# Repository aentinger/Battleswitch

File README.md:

💾 Battleswitch
===============

# 📸 Image

# 📂 Description

A battleswitch is an electronic module which is responsible for the activation/deactivation of weapon systems in combat robots. More generally spoken, a battleswitch is a module which enables the switching of loads using an ordinary remote control.

The LXRobotics Battleswitch enables the control of up to 2 actuators over a single RC remote control channel. The battleswitch is connected to and powered by the RC receiver over a 3-pin connection like a servo and tolerates a wide input voltage range from 2 to 8 V DC with a maximum current consumption of 75 mA. The internal software state of the battleswitch is visualized via LEDs, which greatly simplifies operation and integration of the battleswitch. The assignment which remote control input signal leads to which actuator output, is performed via firmware versions which are generated by LXRobotics upon request.

**Features**

* 1 Remote control channel switches 2 actuators
* Switching capacity per channel: max. 40 V / 5 A @ 100 °C
* Supply of the battleswitch electronics by the RC receiver - no additional power supply terminal necessary
* Wide input voltage range for electronic supply: 2 - 8 V DC
* Status-LEDs signal the internal software state and the current switching status
* POWER-LED lights up when there the battleswitch is supplied with power
* Failsafe - switching off the actuators in the absence of a valid remote control signal
* Freewheeling diodes available - switching of inductive loads possible
* 3 x M3 holes for stable mounting of the Battleswitch
* Small size: 50 x 50 mm (L x W)

# 🎥 [Video](images/battleswitch_demo.mp4)

# 💻 Build
```bash
sudo apt-get install cmake avr-libc binutils-avr gcc-avr avrdude
git clone https://github.com/aentinger/Battleswitch && cd Battleswitch/software
mkdir build && cd build
cmake ..
make
```

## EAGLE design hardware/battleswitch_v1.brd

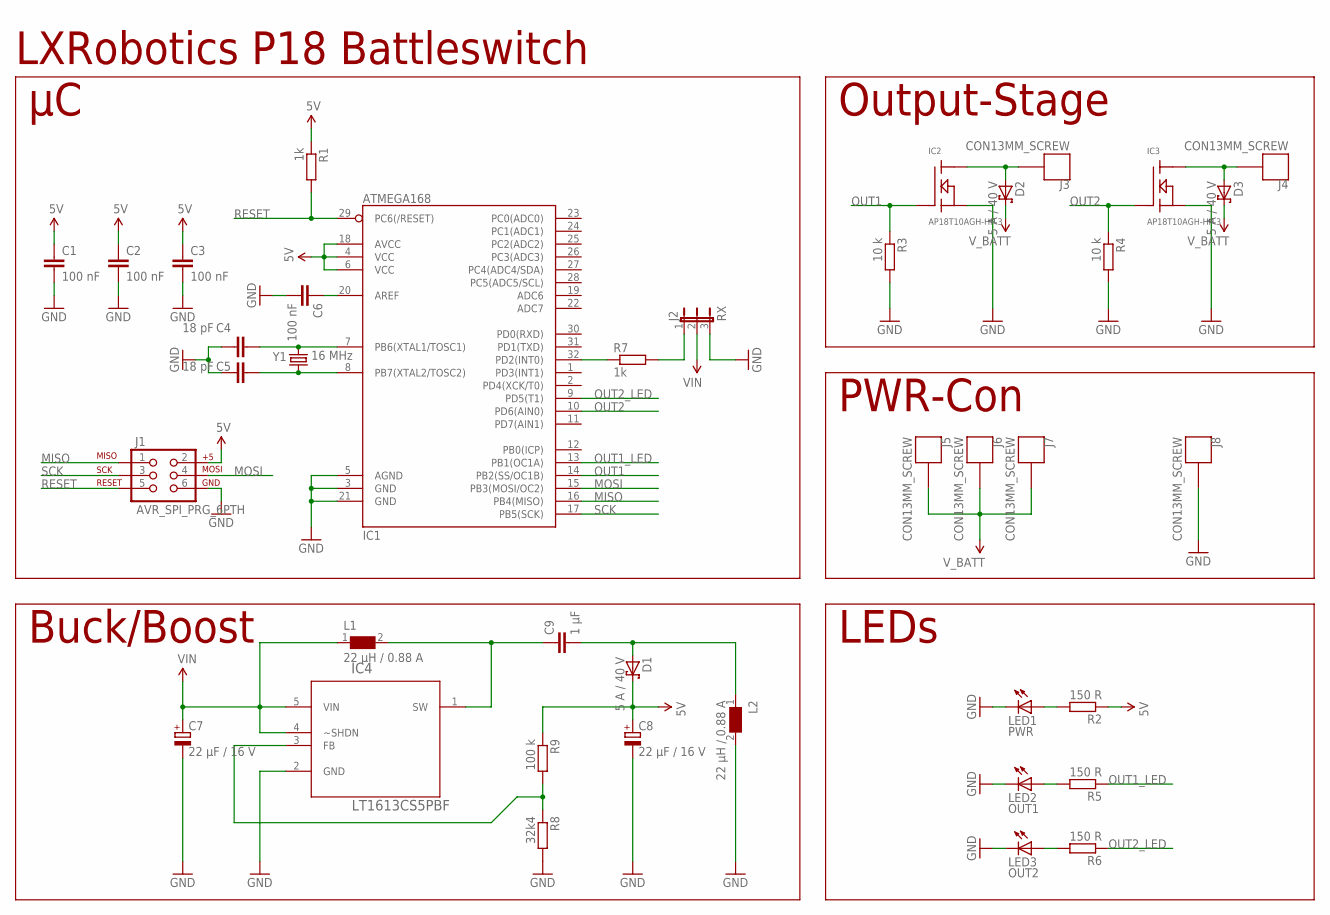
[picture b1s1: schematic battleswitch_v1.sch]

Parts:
C1, C2, C3, C6: 100 nF; C0805
C4, C5: 18 pF; C0805
C7, C8: 22 µF / 16 V; PANASONIC_C
C9: 1 µF; C0805
D1, D2, D3: 5 A / 40 V; SMC
IC1: ATMEGA168; TQFP32-08
IC2, IC3: AP18T10AGH-HF-3; TO252
IC4: LT1613CS5PBF; SOT95P280X145-5N
J1: AVR_SPI_PRG_6PTH; 2X3
J2: RX; JP2
J3, J4, J5, J6, J7, J8: CON13MM_SCREW; CON1_3MM_SCREW
L1, L2: 22 µH / 0.88 A; WE-TPC_4818/4828
LED1: PWR; CHIP-LED0805
LED2: OUT1; CHIP-LED0805
LED3: OUT2; CHIP-LED0805
R1, R7: 1k; R0805
R2, R5, R6: 150 R; R0805
R3, R4: 10 k; R0805
R8: 32k4; R0805
R9: 100 k; R0805
Y1: 16 MHz; HC49US

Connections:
5V: C1.1, C2.1, C3.1, C8.+, D1.C, IC1.4 (VCC), IC1.6 (VCC), IC1.18 (AVCC), J1.2, R1.1, R2.1, R9.1
GND: C1.2, C2.2, C3.2, C4.2, C5.2, C6.2, C7.-, C8.-, IC1.3 (GND), IC1.5 (AGND), IC1.21 (GND), IC2.S, IC3.S, IC4.2 (GND), J1.6, J2.3, J8.P$1, L2.2, LED1.C, LED2.C, LED3.C, R3.2, R4.2, R8.2
MISO: IC1.16 (PB4(MISO)), J1.1
MOSI: IC1.15 (PB3(MOSI/OC2)), J1.4
unnamed: J2.1, R7.2
unnamed: C6.1, IC1.20 (AREF)
unnamed: IC1.32 (PD2(INT0)), R7.1
unnamed: LED2.A, R5.2
unnamed: LED3.A, R6.2
unnamed: D2.A, IC2.D, J3.P$1
unnamed: D3.A, IC3.D, J4.P$1
unnamed: C9.1, IC4.1 (SW), L1.2
unnamed: IC4.3 (FB), R8.1, R9.2
unnamed: C9.2, D1.A, L2.1
unnamed: C4.1, IC1.7 (PB6(XTAL1/TOSC1)), Y1.2
unnamed: C5.1, IC1.8 (PB7(XTAL2/TOSC2)), Y1.1
unnamed: LED1.A, R2.2
OUT1: IC1.14 (PB2(SS/OC1B)), IC2.G, R3.1
OUT1_LED: IC1.13 (PB1(OC1A)), R5.1
OUT2: IC1.10 (PD6(AIN0)), IC3.G, R4.1
OUT2_LED: IC1.9 (PD5(T1)), R6.1
RESET: IC1.29 (PC6(/RESET)), J1.5, R1.2
SCK: IC1.17 (PB5(SCK)), J1.3
VIN: C7.+, IC4.4 (~SHDN), IC4.5 (VIN), J2.2, L1.1
V_BATT: D2.C, D3.C, J5.P$1, J6.P$1, J7.P$1

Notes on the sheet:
Output-Stage
PWR-Con
LEDs
Buck/Boost
LXRobotics P18 Battleswitch

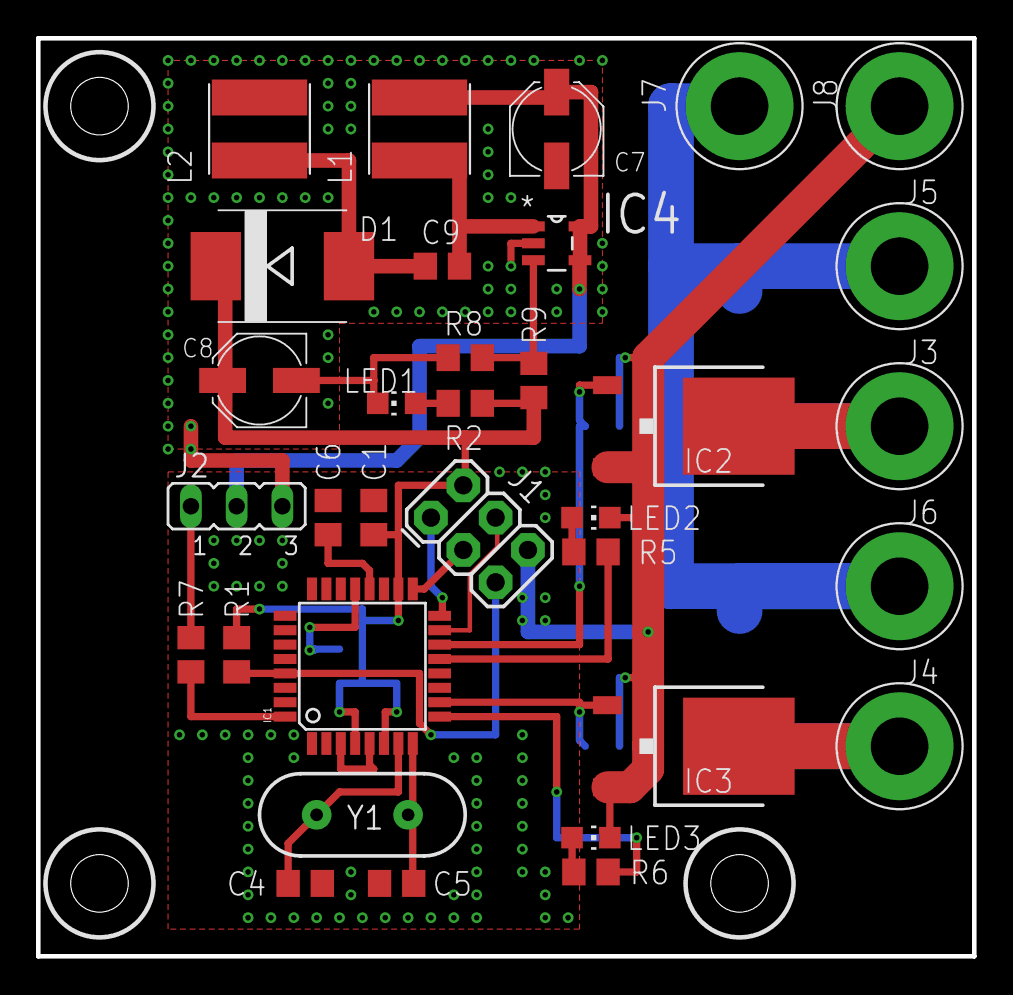
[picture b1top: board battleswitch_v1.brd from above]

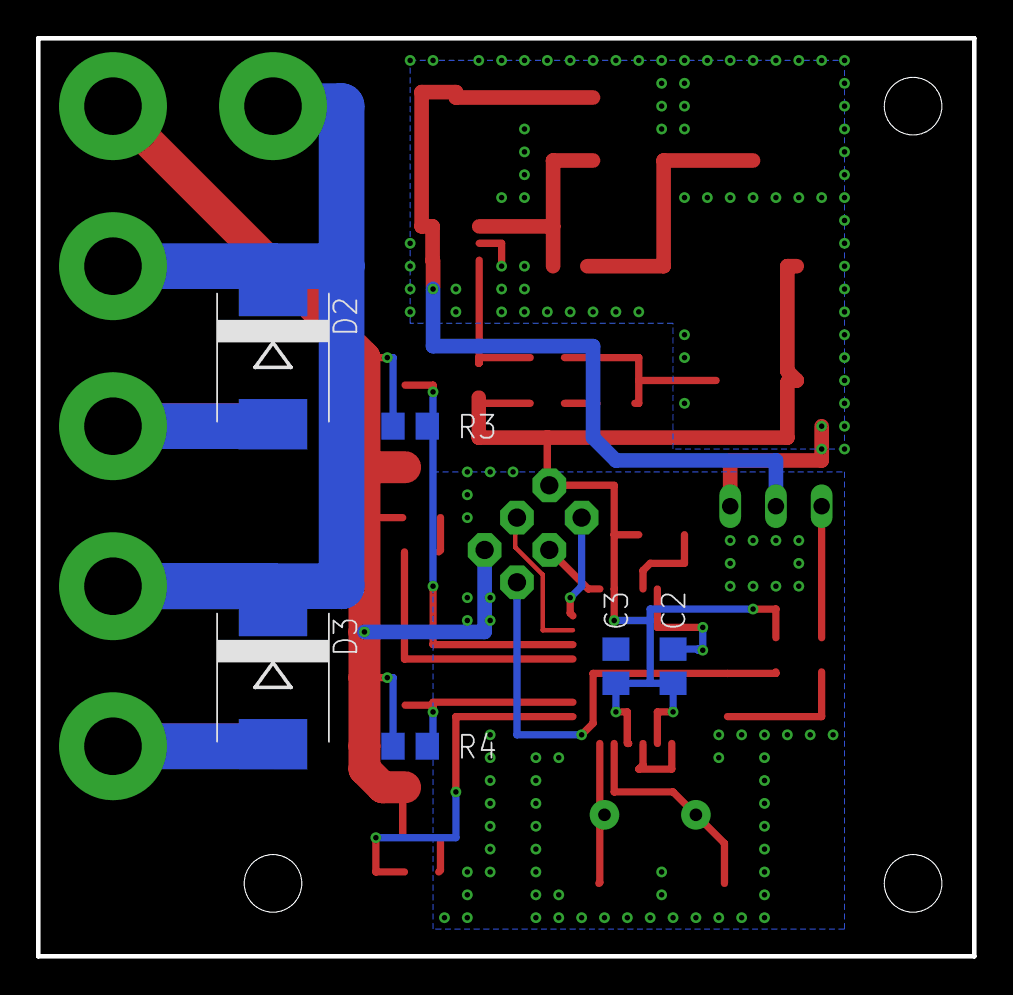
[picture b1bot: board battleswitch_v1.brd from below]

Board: 2 copper layers, 52.0 x 51.0 mm, 39 parts (6 on the bottom side), 25 nets.

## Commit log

2015-07-13 initial checkin of battleshield hardware/binaries
2017-03-02 Adding CMakeLists file for building project with cmaek
2017-03-02 Removing executable rights from source code
2017-03-02 Test
2017-03-02 Trying to change to unix encodigns
2017-03-02 Converting to linux file endings
2017-06-27 Adding hardware + images
2025-03-26 Add video demo.
2025-03-26 Add BOM.
2025-03-26 Pretty up README.
2025-03-26 Fix repo URL.

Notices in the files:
README.md:
License: CC BY-NC-SA 4.0
parts and their libraries:
SparkFun-DigitalIC: Licensing: CC v3.0 Share-Alike You are welcome to use this library for commercial purposes.
